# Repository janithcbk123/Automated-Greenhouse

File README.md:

# Automated-Greenhouse

<p align="left">
  The demand for a system capable of maximizing crops in an efficient and convenient way is higher than ever. The aim of this project is to make an automated greenhouse with IOT that is capable of monitoring, controlling, and automating conditions of crops remotely   and recording data across long periods of time. The core of the product consists of a Raspberry Pi 3b+ microprocessor, a Firebase real-time database, and an Android app. The Raspberry Pi is connected with temperature, humidity, moisture, and light sensors, a        lighting circuit, and relays that control fan, dripping, and sprinkling circuits. The Firebase real-time database acts as the connection between the Raspberry Pi and the Android app. The readings from sensors are uploaded to the firebase and then can be monitored   from the app. The Android app has two main modes of operation, namely manual and automatic. In the manual mode, each of the relays can be switched on or off at any time by the user while in the automatic mode, the system manages the circuits according to a set of   conditions entered by the user. Another feature of this product is saving the readings of sensors along with time so that they can be used for projections and analysis. The multiple modes of operation and advanced features were added to make sure that the product   is accessible to novices and hobbyists while still being a valuable tool for professional-level farming.
</p>

## Acknowledgements
<p align="left">
  This project would not have been possible without the support of many individuals. We would like to give our special appreciation to the project supervisor Mr. Nicoloy Gurusinghea for his guidance and support throughout the project time period. Our special thanks   go to the laboratory staff who allowed us to use the equipment for the completion of our projects and indeed we are thankful for letting us borrow such an expensive Raspberry Pi from the Laboratory for the project use.
</p>

Software Used
- KiCAD 6.0
- Kodular.io
- PyCharm
- Proteus 8 Professional
- Solidworks 2021

## Authors

- [@janithcbk123](https://github.com/janithcbk123)
- [@Thesara97](https://github.com/Thesara97)
- [@NimeshMendis](https://github.com/NimeshMendis)
- [@adiththa](https://github.com/adiththa)
- [@DinushaWerapitiya](https://github.com/DinushaWerapitiya)

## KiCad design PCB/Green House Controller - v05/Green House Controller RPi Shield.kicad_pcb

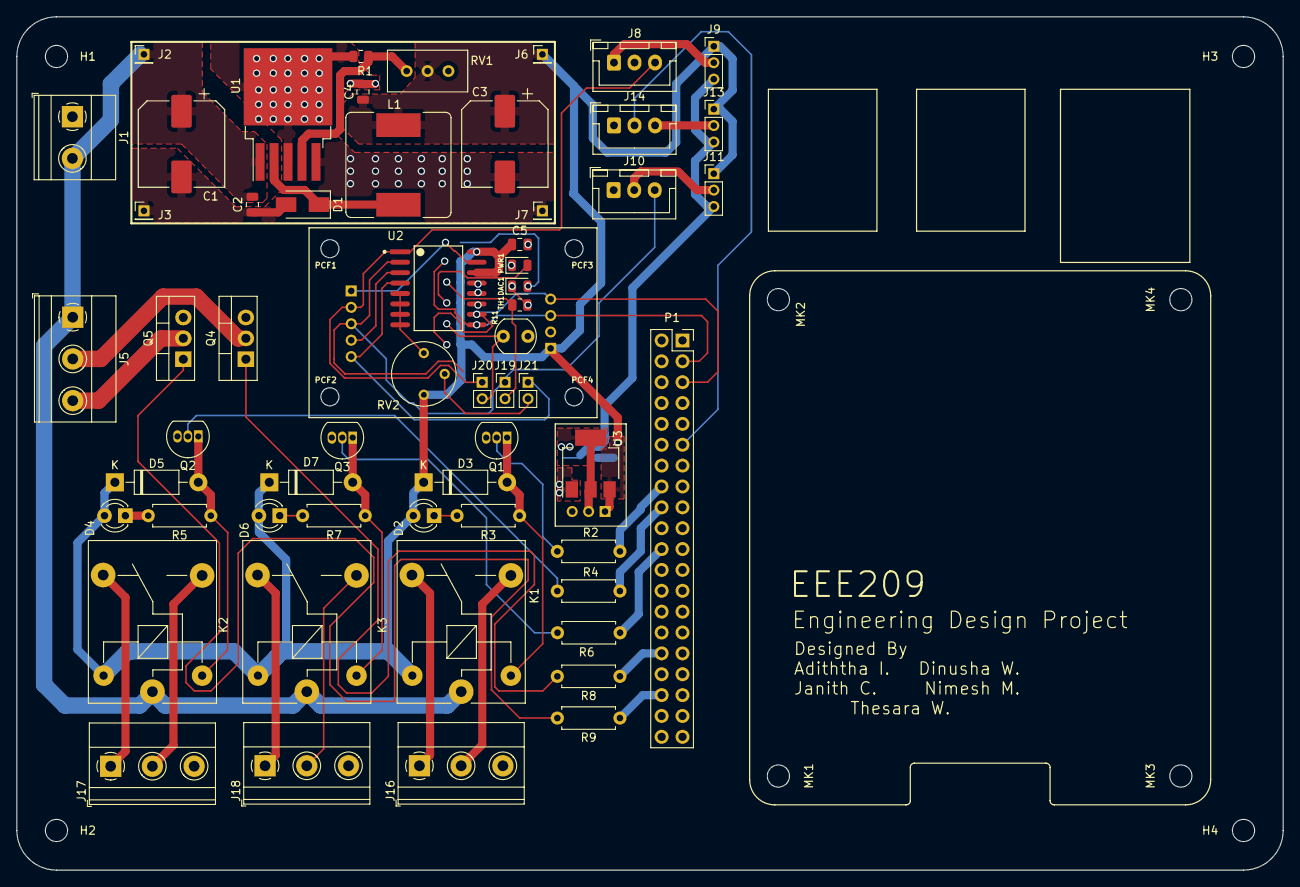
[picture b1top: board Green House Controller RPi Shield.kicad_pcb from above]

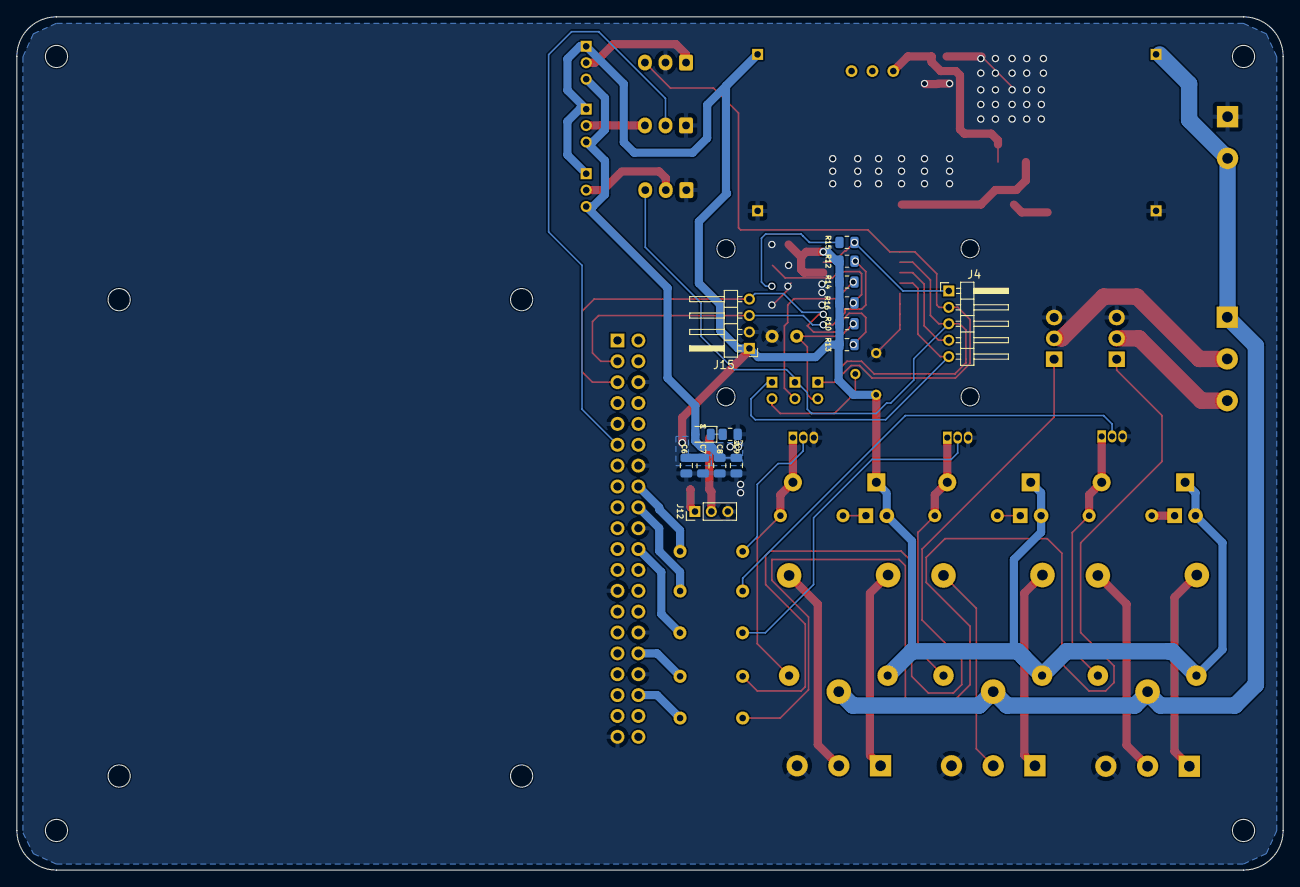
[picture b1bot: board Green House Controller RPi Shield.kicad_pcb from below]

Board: 2 copper layers, 154.2 x 103.9 mm, 85 parts (15 on the bottom side), 49 nets.

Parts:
C1, C3: 330uF; CP_Elec_10x10
C2, C4, C6, C7, C8, C9: 150nF; C_0805_2012Metric
C5: 100nF; C_0805_2012Metric
D1: B120-E3; D_SMA
D2, D4, D6: LED; LED_D3.0mm
D3, D5, D7: 1N4007; D_DO-41_SOD81_P10.16mm_Horizontal
D8: LED; LED_0805_2012Metric
DAC1: LED; LED_0805_2012Metric
H1, H2, H3, H4: MountingHole; MountingHole_2.7mm_M2.5
J1: 12V PWR_IN; TerminalBlock_Phoenix_MKDS-1,5-2-5.08_1x02_P5.08mm_Horizont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
J2: +IN; PinHeader_1x01_P2.00mm_Vertical
J3: -IN; PinHeader_1x01_P2.00mm_Vertical
J4: Conn_01x05_Male; PinHeader_1x05_P2.00mm_Horizontal
J5, J16, J17, J18: Screw_Terminal_01x03; TerminalBlock_Phoenix_MKDS-1,5-3-5.08_1x03_P5.08mm_Horizont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
J6: +OUT; PinHeader_1x01_P2.00mm_Vertical
J7: -OUT; PinHeader_1x01_P2.00mm_Vertical
J8: TEMT6000; JST_XH_B3B-XH-A_1x03_P2.50mm_Vertical
J9, J11, J12, J13: Conn_01x03_Male; PinHeader_1x03_P2.00mm_Vertical
J10: CSMS_V1.2; JST_XH_B3B-XH-A_1x03_P2.50mm_Vertical
J14: DHT11; JST_XH_B3B-XH-A_1x03_P2.50mm_Vertical
J15: Conn_01x04_Male; PinHeader_1x04_P2.00mm_Horizontal
J19, J20, J21: Conn_01x02_Male; PinHeader_1x02_P2.00mm_Vertical
K1, K2, K3: SANYOU_SRD_Form_C; Relay_SPDT_SANYOU_SRD_Series_Form_C
L1: 47uH; L_Bourns_SRR1260
MK1, MK2, MK3, MK4: M2.5; MountingHole_2.7mm_M2.5
P1: Conn_02x20_Odd_Even; PinSocket_2x20_P2.54mm_Vertical
PCF1, PCF2, PCF3, PCF4: M2.2; MountingHole_2.2mm_M2
PWR1: LED; LED_0805_2012Metric
Q1, Q2, Q3: BC547; TO-92_Inline
Q4, Q5: TIP120; TO-220-3_Vertical
R1, R17: 820; R_0805_2012Metric
R2, R4, R6: 1K; R_Axial_DIN0207_L6.3mm_D2.5mm_P7.62mm_Horizontal
R3, R5, R7, R8, R9: 510; R_Axial_DIN0207_L6.3mm_D2.5mm_P7.62mm_Horizontal
R10, R14, R15, R16: 1K; R_0805_2012Metric
R11: A9050; R_LDR_5.0x4.1mm_P3mm_Vertical
R12, R13: 10K; R_0805_2012Metric
RV1: 10K; Potentiometer_Bourns_3296W_Vertical
RV2: 1K; Potentiometer_Bourns_3339P_Vertical
TH1: Thermistor_NTC; R_0805_2012Metric
U1: TO-263-5_TabPin3
U2: PCF8591; NXP_Semiconductors-SOT162-1-02_2016-0-IPC_A
U3: AMS1117; SOT-223-3_TabPin2

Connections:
+3.3VA: P1.1, P1.17
+3V3: C8.1, C9.1, D8.2 (A), J9.3, J11.3, J12.2, J13.3, U3.2 (VO)
+5V: C3.1, C4.1, C5.1, C6.1, C7.1, D2.2 (A), D3.1 (K), D4.2 (A), D5.1 (K), D6.2 (A), D7.1 (K), J6.1, J9.1, J11.1, J12.1, J13.1, J15.1, K1.5, K2.5, K3.5, L1.2, R10.1, R12.1, R13.1, R14.1, R16.1, RV1.2, RV2.3, U2.14 (VREF), U2.16 (VDD), U3.3 (VI)
+5VA: P1.2, P1.4
+12V: C1.1, C2.1, J1.2, J2.1, J5.1, K1.1, K2.1, K3.1, U1.1 (VIN)
/5V-Relay1/NC: J17.1, K2.4
/5V-Relay1/NO: J17.2, K2.3
/5V-Relay2/NC: J18.1, K3.4
/5V-Relay2/NO: J18.2, K3.3
/5V-Relay/NC: J16.1, K1.4
/5V-Relay/NO: J16.2, K1.3
/CSMS: J4.3, J10.3, J19.1, U2.2 (AIN1)
/GPIO2(SDA1): J15.3, P1.3, R12.2, U2.9 (SDA)
/GPIO3(SCL1): J15.4, P1.5, R13.2, U2.10 (SCL)
/GPIO12(PWM0): P1.32, R8.1
/GPIO16: P1.36, R9.1
/GPIO17(GEN0): J14.2, P1.11
/GPIO23(GEN4): P1.16, R2.1
/GPIO24(GEN5): P1.18, R4.1
/GPIO25(GEN6): P1.22, R6.1
/LED Drive/BLUE_OUT: J5.3, Q5.2 (C)
/LED Drive/RED_OUT: J5.2, Q4.2 (C)
/PCF8591_YL40/AIN2: J4.4, U2.3 (AIN2)
/PCF8591_YL40/AIN3: J4.5, J21.1, U2.4 (AIN3)
/PCF8591_YL40/AOUT: J4.1, R15.1, U2.15 (AOUT)
/TEMT6000: J4.2, J8.3, J20.1, U2.1 (AIN0)
GND: C1.2, C2.2, C3.2, C4.2, C5.2, C6.2, C7.2, C8.2, C9.2, D1.2 (A), DAC1.1 (K), J1.1, J3.1, J7.1, J8.2, J10.1, J12.3, J14.1, J15.2, J16.3, J17.3, J18.3, P1.6, P1.9, P1.14, P1.20, P1.25, P1.30, P1.34, P1.39, PWR1.1 (K), Q1.3 (E), Q2.3 (E), Q3.3 (E), Q4.3 (E), Q5.3 (E), R1.2, R11.2, R17.2, RV2.1, TH1.2, U1.3 (GND), U1.5 (~ON/OFF), U2.5 (A0), U2.6 (A1), U2.7 (A2), U2.8 (VSS), U2.11 (OSC), U2.12 (EXT), U2.13 (AGND), U3.1 (ADJ)
unnamed: D1.1 (K), L1.1, U1.2 (OUT)
unnamed: D2.1 (K), R3.2
unnamed: D3.2 (A), K1.2, Q1.1 (C), R3.1
unnamed: D4.1 (K), R5.2
unnamed: D5.2 (A), K2.2, Q2.1 (C), R5.1
unnamed: D6.1 (K), R7.2
unnamed: D7.2 (A), K3.2, Q3.1 (C), R7.1
unnamed: D8.1 (K), R17.1
unnamed: DAC1.2 (A), R15.2
unnamed: J8.1, J9.2
unnamed: J10.2, J11.2
unnamed: J13.2, J14.3
unnamed: J19.2, R14.2, TH1.1
unnamed: J20.2, R10.2, R11.1
unnamed: J21.2, RV2.2
unnamed: PWR1.2 (A), R16.2
unnamed: Q1.2 (B), R2.2
unnamed: Q2.2 (B), R4.2
unnamed: Q3.2 (B), R6.2
unnamed: Q4.1 (B), R8.2
unnamed: Q5.1 (B), R9.2
unnamed: R1.1, RV1.1, U1.4 (FB)

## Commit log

2022-12-08 Add File
2022-12-08 Upload File
2023-09-12 Create LICENSE
